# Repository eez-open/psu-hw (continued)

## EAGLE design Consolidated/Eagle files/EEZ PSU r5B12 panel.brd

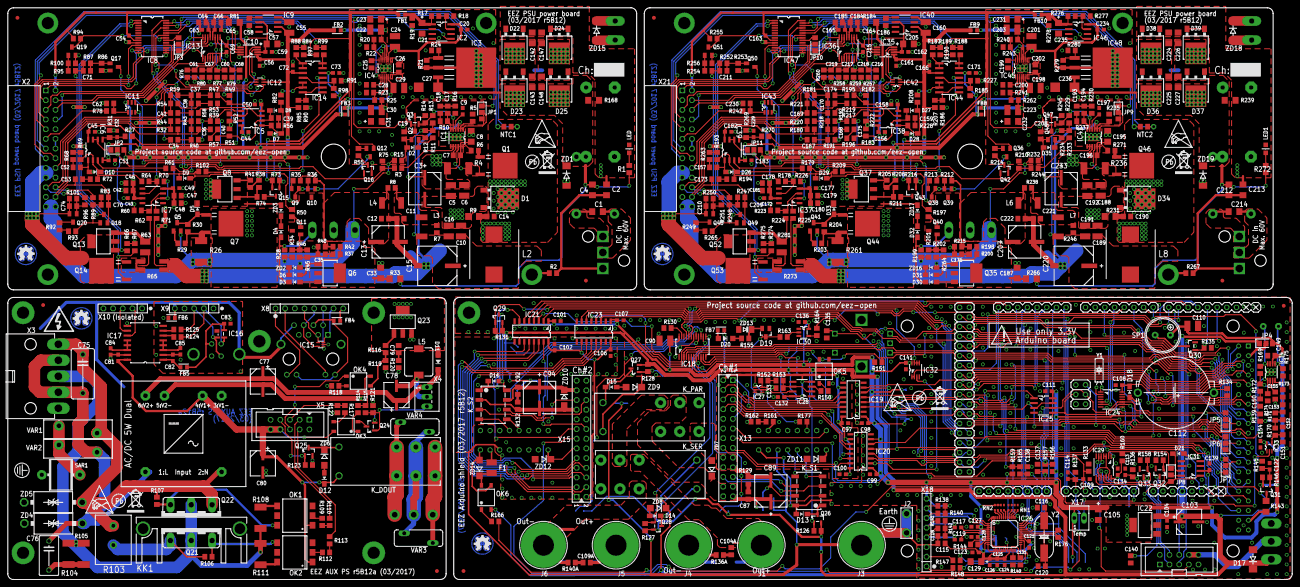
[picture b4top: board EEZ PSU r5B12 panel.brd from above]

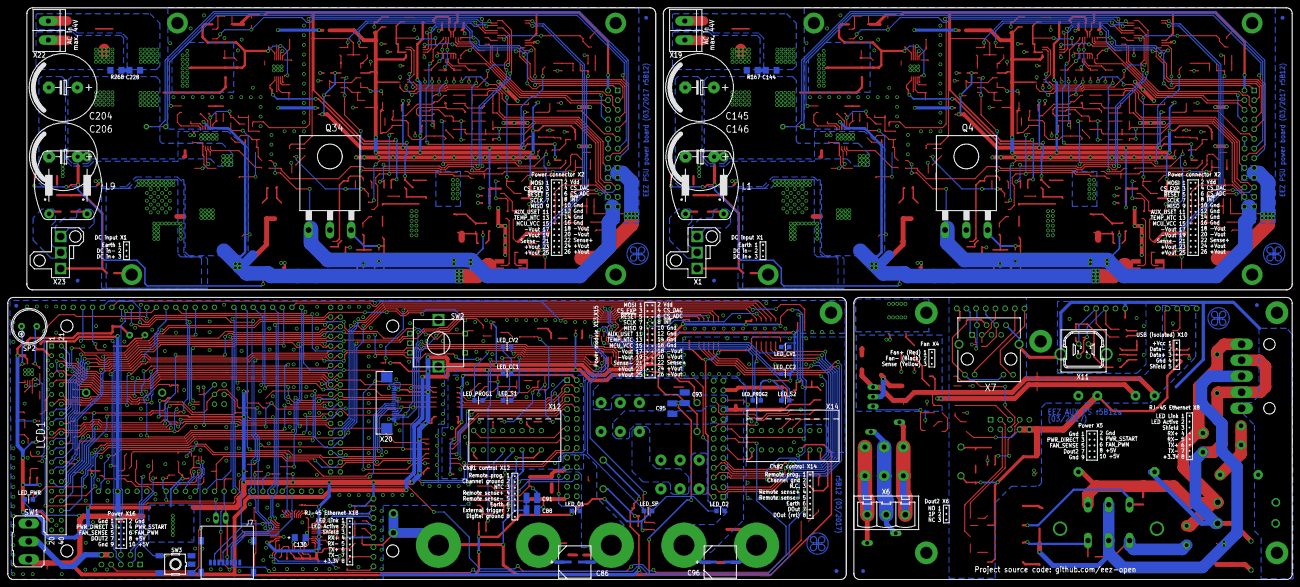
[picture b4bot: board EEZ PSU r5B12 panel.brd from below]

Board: 3 copper layers, 337.0 x 150.0 mm, 815 parts (42 on the bottom side), 579 nets.

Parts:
C1, C2, C4, C212, C213, C214: 4n7/100V; C1206
C3, C86, C96, C233: 50SVPF18M; CAPAE830X650N
C5, C6, C188, C192: 4u7/100V; C1210
C7, C87, C92, C150, C153, C196: 470n; C0805
C8, C33, C187, C195: 1u/100V; C1206
C9, C20, C32, C43, C44, C45, C49, C50, C51, C54, C56, C59, C63, C65, C69, C72, C73, C81, C82, C83, C84, C85, C97, C98, C99, C100, C101, C102, C104, C106, C107, C108, C109, C111, C113, C114, C121, C122, C123, C124, C125, C126, C127, C128, C132, C134, C136, C139, C141, C154, C156, C158, C161, C162, C163, C164, C165, C166, C171, C172, C177, C182, C183, C197, C215, C229, C234: 100n; C0603
C10, C16, C22, C24, C29, C30, C55, C90, C110, C160, C189, C191, C198, C201, C203, C223: 10u; C1210
C11, C26, C46, C48, C58, C64, C66, C104A, C109A, C149, C178, C180, C184, C185, C186, C202, C221: 1u; C0805
C12, C62, C222, C230: n.c.; C0805
C13, C207: EEEFK1H470P; CAPAE830X1050N
C14, C19, C190, C208: 470p; C0805
C15, C220: EEEFK1J101P; PANASONIC_F
C17, C39, C159, C194: 120p; C0805
C18, C151, C152, C193: 4n7; C0805
C21, C130, C235: 4u7; EC1206
C23, C31, C57, C105, C129, C205, C231, C232: 10u; EC1206
C25, C28, C35, C42, C47, C70, C74, C118, C131, C135, C137, C138, C176, C179, C181, C199, C200, C209, C210: 10n; C0805
C27, C236: 1uF/50V Tant.; C/6032-28R
C34, C41, C167, C169: 47p; C0805
C36, C37, C38, C40, C71, C168, C170, C174, C175, C211: 2n2; C0805
C52, C53, C157, C173: 1n; C0805
C60, C61, C67, C68, C216, C217, C218, C219: 3n3; C0805
C75: 6n8 (X1); C102-064X133
C76: 47n/400V; C075-052X106
C77, C80, C103: 47u; CAPAE660X610N
C78: 220u; CAPAE660X610N
C79, C133, C140: 47n; C0805
C88, C91, C93, C95: 4n7/100V; C1210
C89, C94: UWT1H220MCL; CAPAE830X650N
C112: EECS5R5H105; SG-R20MM
C115: 22n; C0805
C116, C120: 18p; C0805
C117, C119: 6n8; C0603
C142, C143, C147, C148, C224, C225, C226, C227: 1n; C1206
C144, C228: n.c; C1206
C145, C146, C204, C206: 2m2; ECAP7.5/18
C155: 220n; C0805
D1, D34: STPS15H100; TO252
D2, D3, D4, D5, D6, D7, D8, D9, D10, D12, D13, D14, D15, D16, D18, D21, D26, D27, D28, D29, D30, D31, D32, D33, D35: BAS316; SOD323-W
D11, D20: SKL16; SOD123
D17: SMBJ5.0A-TR; DO214AA
D19: BAT54S; SOT23
D22, D23, D24, D25, D36, D37, D38, D39: STPS15H100; TO252@1
EEZ_SIGNATURE, EEZ_SIGNATURE1, EEZ_SIGNATURE2, EEZ_SIGNATURE3: SIGNATURESMALL; SIGNATURE_5MM
F1: 50mA; F1210
FB1, FB2, FB3, FB4, FB5, FB6, FB7, FB8, FB9, FB10: 60R@100MHz; BEAD0603
FM1, FM2, FM3, FM4, FM5, FM6, FM7, FM8: FIDUCIAL_2; FIDUCIAL_DUAL
IC1, IC41: LTC3864EMSE#PBF; LTC_05-08-1666
IC2, IC46: LP2951SO8; SOIC127P600X175-8N
IC3, IC48: TL783CKTTR; TO254P1524X483-4N
IC4, IC45: LTC3260EMSE#PBF; SOP50P490X110-17N
IC5, IC6, IC38, IC39: TL072D; SOIC127P600X173-8N
IC7, IC37: LTC2050HVCS8#PBF; SOIC127P600X173-8N
IC8, IC47: MCP23S17-E/SS; SOP65P780X200-28N
IC9, IC40: REF5025AIDG4; SOIC127P600X175-8N
IC10, IC35: DAC8552IDGKTG4; DGK8-M
IC11, IC43: ADG465SOT-23; SOT95P280X145-6N
IC12, IC42: TS5A9411DCKT; SOT65P210X110-6N
IC13, IC36: ADS1120IPWR; PW(R-PDSO-G16)
IC14, IC44: LP339D; SOIC127P600X175-14N
IC15: TPD4E002DRL; DRL5
IC16: TPD2E001DZDR; SOP192P292X122-4N
IC17: ADUM3160BRWZ; SOIC-16W
IC18: TLC5925IDBQR; SOP63P600X175-24N
IC19, IC23: Si8641EC-B-IS1; SOIC-16
IC20, IC21: SI8651EC-B-IS1; SOIC-16
IC22: LD1117ADT33TR; SOT223
IC24: PCA21125T/Q900/1,1; SOP65P640X120-14N
IC25: AT25256B-SSHL-B; SOIC127P600X175-8N
IC26: W5500; TQFP48-7X7
IC27: BC857BS; SOT65P210X110-6N
IC28: TLC555; SOIC127P600X175-8N
IC29: SN74LVC08APWR; SOP65P640X120-14N
IC30: SN74LV1T34DBVR; SOT95P280X145-5N
IC31: TPS3705-33D; SOIC127P600X175-8N
IC32: SN74LVC2G02DCTR; SOP65P400X130-8N
IC33: 74LVC1G125GW.125; SOT65P210X110-5N
IC34: TPA6205A1DGN; SOP65P490X110-9N
J1, J5: BS-244DSM-R; BP_5_12
J2: 1-726388-2; PCB_TAB-4.8MM
J3: BS-244DSM-G; BP_5_12
J4, J6: BS-244DSM-B; BP_5_12
J7: 693072010801
JP1, JP2, JP3, JP4, JP5, JP6, JP7, JP8, JP9, JP10, JP11: 0R-JUMPA; A0R-JMP
KK1: SK 145/37,5; SK145
K_DOUT: RT424005; RT-C/016A5_ROUND
K_PAR: RT424005; RT-C/016A5_ROUND
K_S1, K_S2: G6K-2F-5DC; G6K-2F
K_SER: RT424005; RT-C/016A5_ROUND
L1, L9: RN112-4-02; RN112
L2, L8: 7443551331; WE-HCI_1350/1365
L3, L4, L6, L7: IHLP2020CZER3R3M11; IHLP-2020BZ-11
L5: 470u; DE0704
LCD1: TFT_320QVT; LCD_TFT_9341_MIRROR
LED, LED1: n.c.; LED_HSMH-C170
LED_CC1, LED_CC2: HSMH-C170; LED_HSMH-C170
LED_CV1, LED_CV2: HSMY-C170; LED_0805
LED_O1, LED_O2: HSMG-C170; LED_0805
LED_PROG1, LED_PROG2: HSMH-C170; LED_HSMH-C170
LED_PWR: HSMD-C170; LED_0805
LED_S1, LED_S2: HSMY-C170; LED_0805
LED_SP: HSMH-C170; LED_HSMH-C170
MCU: Arduino Due; ARDUINO+ICSP_MIRROR
NTC1, NTC2: 10K/Beta:3570K; R_0204/5+0805
OK1: MOC3052; DIL6-SMD
OK2: MOC3062; DIL6-SMD
OK3, OK4, OK5, OK6: HCPL-181
Q1, Q7, Q44, Q46: IRFR5305; TO229P990X239-3N
Q2, Q9, Q10, Q18, Q38, Q39, Q45, Q49: MMBT5401; SOT23-BEC
Q3, Q16, Q24, Q25, Q30, Q32, Q33, Q42, Q47: 2N7002; SOT103P240X110-3N
Q4, Q34: IRFP250N; TO247BH-CLR
Q5, Q41: BC857C; SOT23-BEC
Q6, Q8, Q35, Q37: BCP56-16.115; SOT230P700X180-4N
Q11, Q12, Q17, Q19, Q20, Q36, Q40, Q48, Q50, Q51: MMBT5551; SOT23-BEC
Q13, Q23, Q52: IRLL2705PBF; SOT223
Q14, Q53: IRFR48ZPBF; TO229P990X239-3N
Q15, Q26, Q27, Q28, Q29, Q31, Q43: IRLML2246TRPBF; SOT95P237X112-3N
Q21, Q22: BTA26-600; TOP3S-1
R1, R2, R14, R160, R245, R267, R272: n.c.; R0805
R3, R10, R11, R19, R27, R40, R49, R51, R58, R64, R69, R72, R74, R82, R91, R94, R95, R98, R102, R121, R122, R139, R145, R149, R157, R165, R172, R173, R178, R182, R183, R185, R191, R192, R193, R194, R208, R209, R211, R227, R233, R237, R244, R254, R255, R270, R278: 10K; R0805
R4, R236: R010/2W; R2512
R5, R66, R67, R85, R86, R87, R100, R154, R158, R174, R207, R235, R252, R253, R256, R274, R275: 47K; R0805
R6, R129, R132, R136A, R140A, R271: 1R; R0805
R7, R8, R42, R116, R155, R198, R238, R246: 100R; R0805
R9, R33, R81, R143, R184, R231, R266: 10R; R1206
R12, R15, R22, R23, R73, R75, R123, R135, R146, R210, R216, R232, R234, R241, R243: 100K; R0805
R13, R20, R25, R229, R240, R262: 330K; R0805
R16, R126, R127, R128, R131, R133, R136, R137, R156, R159, R161, R162, R230: 4K7; R0805
R17, R34, R201, R276: 16K; R0805
R18, R84, R97, R189, R190, R277: 5K1; R0805
R21, R31, R35, R36, R41, R47, R57, R76, R77, R79, R80, R110, R113, R118, R166, R177, R195, R196, R205, R212, R213, R257, R258, R259, R260, R269, R279: 220R; R0805
R24, R55, R130, R151, R214, R280: 1K8; R0805
R26, R261: 2R2/2W; R2512
R28, R38, R68, R78, R92, R114, R120, R163, R164, R170, R171, R199, R206, R242, R249, R263: 1K; R0805
R29, R30, R32, R45, R59, R61, R90, R93, R106, R107, R119, R179, R180, R181, R186, R203, R204, R264, R265: 2K2; R0805
R37, R50, R197, R200: 470R; R0805
R39, R52, R217, R222: 7K5 0.1%; R0805
R43, R53, R218, R219: 100K 0.1%; R0805
R44, R54, R220, R221: 24K 0.1%; R0805
R46, R89, R96, R152, R153, R202, R248, R251: 750R; R0805
R48, R215: 51K; R0805
R56, R228: 0R; R0805
R60, R70, R223, R226: 2K 0.1%; R0805
R62, R71, R224, R225: 82R 0.1%; R0805
R63, R281: 0R16; R1210
R65, R273: 0R020 (1-3W); R_2512-4WIRE
R83, R101, R247, R250: 330R; R0805
R88, R99, R115, R117, R187, R188: 5K6; R0805
R103: 18-22R/7W; R_0913
R104, R105, R108, R111: 330R/2W; R2512
R109, R112, R138, R140, R141, R142: 49R9; R0805
R124, R125: 22R; R0805
R134, R147, R148, R150: 180R; R0805
R144: 12K4; R0805
R167, R268: n.c.; R1206
R168, R239: 12K; R1206
R169, R175: 20K; R0805
R176: 1M; R0805
RN1, RN2: 4x10K; CAY16
SAR1: CG2-470L; SAR
SH1, SH4: Pgnd to Pout- short; SHORT_NOHOLE
SH2, SH5: Sgnd to Pgnd short; SHORT_NOHOLE
SH3: SHORT_NOHOLE
SP1, SP2: LD-BZEN-0903
SW1: A101SYCQ04; M9040P
SW2: PEC12R-4225F-S0024; EC12E_SW
SW3: 1301.9316; TACTM-6XN
TR1: VTX-214-005-0512; PCB_ACDC_VTX_5W_DUAL
U$1, U$2, U$8, U$11: RECYCLE_BIN1/8
U$3, U$5, U$9, U$12: PB_SMALL
U$4, U$6, U$7, U$10: ESD_SYMBOL
VAR1, VAR2: ERZE14A431; VARISTOR
VAR3, VAR4: ERZE11A431; VARISTOR_13MM
X1, X23: 39-30-1039; MINIFIT_39301039
X2, X21: SSW-113-02-T-D-RA
X3: 39303055; MINIFIT_6659-5
X4: 22-23-2031
X5, X16: 09185067324; IDC-10PIN
X6: CTB9300/3A + CTB92VG/3S; WR-TBL_3-PIN
X7: Amphenol: LMJ2138812S0LOT6C or WE: 74990101210; RJ45-VERT
X8: 826629-8; HEADER_8-PIN
X9, X10: 826629-5; SSW-105-02-S-S
X11: 2411-01; KUSBVX-BS1N
X12, X14: MC000006; MC000006_MIRROR
X13, X15: TSW-113-07-F-D
X17: 22-23-2021
X18: MC34753; HEADER_8-PIN
X19, X22: 282836-2; TBLOCK5.0_2
X20: PCA-6B-20-HL-3 or 52746-2071; FPC-20_ROTATED
Y1: 32.768kHz; R26_XTAL
Y2: 25MHz; HC-49/4H
ZD1, ZD19: SMAJ51A; DO214AA
ZD2, ZD16: BZX384-C15; SOD323-W
ZD3, ZD17: PDZ6.2B; SOD323-W
ZD4, ZD5: 1.5KE400CA; DO201-BIDIR
ZD6, ZD8, ZD9, ZD11, ZD12, ZD14: SMAJ18A; DO214AC
ZD7, ZD10: P4SMAJ48A; DO214AC
ZD13: 4V3; MINIMELF
ZD15, ZD18: n.c.; DO214AA

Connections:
0V: C77.2, Q23.3, Q24.2, R119.1, R120.1, R121.2, TR1.5
1V2O: C131.2, IC26.22
!ADC1_SELECT: IC20.4, MCU.15
!ADC2_SELECT: IC23.4, MCU.48
!BP_OE: IC18.21, MCU.10
!BP_OUT0: IC18.5, LED_CV1.C
!BP_OUT1: IC18.6, Q26.1, R126.1
!BP_OUT2: IC18.7, LED_O1.C
!BP_OUT3: IC18.8, LED_SP.C
!BP_OUT4: IC18.9, LED_PROG1.C
!BP_OUT5: IC18.10, LED_S1.C
!BP_OUT6: IC18.11, LED_CC1.C
!BP_OUT7: IC18.12, LED_CV2.C
!BP_OUT8: IC18.13, Q28.1, R127.1
!BP_OUT9: IC18.14, Q27.1, R128.1
!BP_OUT10: IC18.15, LED_CC2.C
!BP_OUT12: IC18.17, LED_S2.C
!BP_OUT13: IC18.18, LED_O2.C
!BP_OUT14: IC18.19, Q29.1, R131.1
!BP_OUT15: IC18.20, LED_PWR.C
!CH1_ADC: IC20.13, X13.6
!CH1_DAC: IC19.12, X13.4
!CH1_EXPANDER: IC19.13, X13.3
!CH1_INT: IC20.11, X13.8
!CH1_RESET: IC20.14, X13.5
!CH2_ADC: IC23.13, X15.6
!CH2_DAC: IC21.12, X15.4
!CH2_EXPANDER: IC21.13, X15.3
!CH2_INT: IC21.11, X15.8
!CH2_RESET: IC23.14, X15.5
!CONVEND1: IC20.6, MCU.21
!CONVEND2: IC21.6, MCU.20
!DAC1_SELECT: IC19.5, MCU.16
!DAC2_SELECT: IC21.5, MCU.47
!DP_DRIVE: Q8.1, R38.1, R74.1
!DP_DRIVE1: Q37.1, R206.1, R211.1
!EEPROM_SELECT: IC25.1, MCU.49
!ETH_IRQ: IC26.36, MCU.18
!ETH_SELECT: IC26.32, MCU.11
!INT: JP3.2, X2.8
!INT1: JP10.2, X21.8
!IO_EXPANDER1: IC19.4, MCU.17
!IO_EXPANDER2: IC21.4, MCU.46
!LCD_INT: MCU.50, X20.7
!LCD_PD: MCU.51, X20.8
!MR: C140.2, IC31.1, JP8.1, SW3.3, SW3.4
!PS_DRDY: IC13.14, JP3.3
!PS_DRDY1: IC36.14, JP10.3
!PS_RESET: IC8.18, X2.5
!PS_RESET1: IC47.18, X21.5
!RESET: D21.A, IC20.3, IC23.3, IC26.37, IC29.1, MCU.RESET
!RST_OUT: IC29.3, IC29.4, IC29.9, IC29.13
!RTC_IRQ: IC24.5, MCU.19
!SET_100%: IC8.24, Q3.1
!SET_100%1: IC47.24, Q47.1
!SET_DP: IC8.22, Q15.1, R73.2
!SET_DP1: IC47.22, Q43.1, R216.2
+3V3: C90.1, C98.1, C99.1, C101.1, C105.+, C107.1, C110.2, C111.1, C115.1, C121.2, C123.1, C124.1, C125.1, C126.1, C127.1, C128.1, C129.+, C134.2, C136.1, C139.2, C141.1, C149.2, C154.2, D18.A, IC18.24, IC19.1, IC20.1, IC20.7, IC21.1, IC21.7, IC22.4, IC23.1, IC25.3, IC25.7, IC25.8, IC26.4, IC26.8, IC26.11, IC26.15, IC26.17, IC26.21, IC26.28, IC29.14, IC30.5, IC31.2, IC32.8, IC33.5, IC34.6, J7.4, JP4.3, Q31.2, R138.1, R139.2, R140.2, R146.2, R151.1, R156.1, R159.1, R160.2, RN2.6, RN2.7, RN2.8, SP1.+B, X13.15, X15.15, X17.1, X18.8, X20.1, X20.17, X20.18
+5V: C54.1, C63.2, C64.2, C80.1, C81.1, C103.1, C104.1, D12.C, D17.C, FB1.P$2, FB7.P$1, IC8.9, IC13.13, IC17.16, IC22.3, JP4.1, K_DOUT.A1, LED_CC1.A, LED_CC2.A, LED_CV1.A, LED_CV2.A, LED_O1.A, LED_O2.A, LED_PROG1.A, LED_PROG2.A, LED_PWR.A, LED_S1.A, LED_S2.A, LED_SP.A, MCU.5V, OK1.1, OK2.1, OK3.4, Q12.B, Q15.2, Q26.2, Q27.2, Q28.2, Q29.2, R73.1, R84.2, R94.2, R97.2, R126.2, R127.2, R128.2, R131.2, SW1.3, TR1.4, X2.2, X5.8, X5.10
+5V1: C163.1, C165.2, C185.2, FB10.P$2, IC36.13, IC47.9, Q36.B, Q43.2, R189.2, R190.2, R216.1, R255.2, X21.2
+12VDC: C77.1, C78.1, D11.C, OK4.4, R114.1, R115.1, TR1.6, X4.1
+VNR: C20.1, C24.1, IC2.8, IC3.2, IC3.4, IC4.1, IC4.11, IC4.13, R21.1
+VNR1: C201.1, C234.1, IC45.1, IC45.11, IC45.13, IC46.8, IC48.2, IC48.4, R279.1
+VREF: C57.+, C59.2, C69.2, IC9.6, IC10.2, IC13.9, R27.1
+VREF1: C162.2, C205.+, C215.2, IC35.2, IC36.9, IC40.6, R270.1
-5VOUT: C30.2, C31.-, FB3.P$1, IC4.5, R25.2
-5VOUT1: C223.2, C232.-, FB8.P$1, IC45.5, R262.2
-12V: C29.1, IC4.6, R38.2, R41.2
-12V1: C198.1, IC45.6, R205.2, R206.2
AC_EARTH: FB6.P$1, SAR1.P$2, X3.1, X7.8, X7.SH1, X7.SH2, X9.5, X11.M1, X11.M2, ZD4.C, ZD5.C
AC_IN1: C147.1, C148.2, D24.3, D25.1, D25.2, R167.2, X19.1, ZD15.A
AC_IN2: C142.1, C143.2, C144.1, D22.3, D23.1, D23.2, X19.2, ZD15.C
AC_IN3: C224.1, C225.2, C228.1, D36.1, D36.2, D38.3, X22.2, ZD18.C
AC_IN4: C226.1, C227.2, D37.1, D37.2, D39.3, R268.2, X22.1, ZD18.A
AC_IN_L: C75.1, Q22.A1, R103.1, R107.2, TR1.2, VAR1.P$2, X3.5, ZD5.A
AC_NEUTRAL: C75.2, C76.1, TR1.1, VAR2.P$1, X3.2, X3.4, ZD4.A
AC_OUT_L: Q21.A2, Q22.A2, R104.1, R105.1, R108.2, R111.2, X3.3
AUDIO_OUT: IC33.2, X20.10
AUX1_USET_IN: X12.8, X12.8.1, X13.11, ZD11.C
AUX2_USET_IN: X14.8, X14.8.1, X15.11, ZD12.C
AUX_+3V3: FB4.P$2, X8.8
AUX_ETH_ACTLED: X7.10, X8.2
AUX_ETH_IN+: IC15.4, X7.3, X8.4
AUX_ETH_IN-: IC15.5, X7.6, X8.5
AUX_ETH_LINKLED: X7.12, X8.1
AUX_ETH_OUT+: IC15.1, X7.2, X8.6
AUX_ETH_OUT-: IC15.3, X7.1, X8.7
AUX_FAN_CTRL: OK4.1, X5.6
AUX_FAN_SENSE: R117.2, R122.1, X5.5
AUX_PWR_DIRECT: R110.2, X5.3
AUX_PWR_SSTART: R113.2, X5.4
AUX_USET_IN: R78.2, X2.11
AUX_USET_IN1: R242.2, X21.11
AUX_USET_SW: IC8.25, IC12.1
AUX_USET_SW1: IC42.1, IC47.25
BATT_NTC: MCU.A4, OK5.4, R151.2
BP_SELECT: IC18.4, MCU.9
BUZZER: MCU.12, Q30.1, R135.2
CC_ACTIVE: IC8.23, R97.1, R99.2
CC_ACTIVE1: IC47.23, R188.2, R190.1
CH1_GND: C97.2, C100.2, C132.2, C133.1, IC19.9, IC19.15, IC20.9, IC28.1, OK5.2, X12.7, X12.7.1, X13.10, X13.12, X13.14, ZD11.A
CH1_MISO: IC19.11, X13.9
CH1_MOSI: IC19.14, X13.1
CH1_SCLK: IC20.12, X13.7
CH1_SYNC: IC20.15, X13.16
CH1_VDD: C97.1, C100.1, C132.1, IC19.10, IC19.16, IC20.10, IC20.16, IC27.1, IC27.4, IC28.4, IC28.8, X13.2
CH2_GND: C102.2, C106.2, IC21.9, IC23.9, IC23.15, X14.7, X14.7.1, X15.10, X15.12, X15.14, ZD12.A
CH2_MISO: IC23.11, X15.9
CH2_MOSI: IC21.14, X15.1
CH2_SCLK: IC23.12, X15.7
CH2_SYNC: IC21.15, X15.16
CH2_VDD: C102.1, C106.1, IC21.10, IC21.16, IC23.10, IC23.16, X15.2
CS_ADC: IC13.2, X2.6
CS_ADC1: IC36.2, X21.6
CS_DAC: IC10.5, X2.4
CS_DAC1: IC35.5, X21.4
CS_EXPANDER: IC8.11, X2.3
CS_EXPANDER1: IC47.11, X21.3
CURR_5A: IC8.1, Q14.1, R67.2
CURR_5A1: IC47.1, Q53.1, R274.2
CURR_500MA: IC8.2, Q13.1, R66.2
CURR_500MA1: IC47.2, Q52.1, R275.2
CV_ACTIVE: IC8.26, R84.1, R88.2
CV_ACTIVE1: IC47.26, R187.2, R189.1
D+: IC16.2, R125.1, X9.3, X11.3
D-: IC16.3, R124.1, X9.2, X11.2
DC+: C1.2, L1.2, X1.3
DC+1: C214.2, L9.2, X23.3
DC-: C1.1, L1.1, X1.2
DC-1: C214.1, L9.1, X23.2
DC_BIAS: C33.1, Q6.2, Q6.4, R33.2, R35.2, R36.2
DC_BIAS1: C187.1, Q35.2, Q35.4, R212.2, R213.2, R266.2
DC_OUT: C3.1, C4.2, C5.1, C6.1, C7.2, C8.1, C27.+, C143.1, C145.+, C146.+, C148.1, D23.3, D25.3, IC1.11, IC3.3, L1.3, R1.2, R4.1, R33.1, R168.1, ZD1.C
DC_OUT1: C188.1, C192.1, C195.1, C196.2, C204.+, C206.+, C212.2, C225.1, C227.1, C233.1, C236.+, D36.3, D37.3, IC41.11, IC48.3, L9.3, R236.1, R239.1, R266.1, R272.2, ZD19.C
DOUT1: MCU.A11, R166.1
DOUT2: IC29.5, MCU.A3
DP_LED: Q15.3, R74.2
DP_LED1: Q43.3, R211.2
EARTH: C2.2, C4.1, C88.2, C91.1, C93.2, C95.1, C115.2, C118.2, J2.P$1, J2.P$2, J3.P$1, R2.2, X1.1, X12.3, X12.3.1, X14.3, X14.3.1, X18.3
EARTH1: C212.1, C213.2, R267.2, X23.1
ENC_A: C137.2, MCU.A8, R157.1
ENC_B: C138.1, MCU.A9, R165.1
ENC_SW: C135.2, MCU.A10, SW2.D
ETH_ACTLED: IC26.27, R147.1
ETH_IN+: C119.1, R142.1, X18.4
ETH_IN-: C117.1, R141.2, X18.5
ETH_LINKLED: IC26.25, R148.1
ETH_OUT+: IC26.2, R140.1, X18.6
ETH_OUT-: IC26.1, R138.2, X18.7
EXTSD_CS: J7.2, MCU.A12
EXT_TRIG: MCU.A7, R164.1
FAN_OUT: C79.2, D11.A, L5.2, Q23.2, Q23.4
FAN_PWM: MCU.6, X16.6
FAN_SENSE: MCU.13, X16.5
FB: IC1.5, Q3.2, R13.2, R14.2, R16.1
FB1: IC41.5, Q47.2, R229.2, R230.1, R245.2
GCOM: JP2.2, R39.1, R60.1
GCOM1: JP11.2, R217.1, R223.1
GND: C2.1, C3.2, C5.2, C6.2, C8.2, C10.2, C15.2, C16.2, C20.2, C21.-, C22.2, C23.-, C24.2, C25.1, C27.-, C28.1, C29.2, C30.1, C31.+, C32.2, C33.2, C35.2, C42.1, C43.2, C44.1, C45.1, C46.1, C47.1, C48.1, C49.2, C50.1, C51.1, C54.2, C55.2, C56.1, C57.-, C58.2, C59.1, C60.1, C61.2, C62.1, C63.1, C64.1, C65.1, C66.1, C67.1, C68.1, C69.1, C72.1, C73.1, C80.2, C81.2, C84.2, C90.2, C98.2, C99.2, C101.2, C103.2, C104.2, C105.-, C107.2, C108.1, C109.1, C110.1, C111.2, C112.2, C113.1, C114.1, C116.2, C120.2, C121.1, C122.1, C123.2, C124.2, C125.2, C126.2, C127.2, C128.2, C129.-, C131.1, C134.1, C135.1, C136.2, C137.1, C138.2, C139.1, C140.1, C141.2, C142.2, C145.-, C146.-, C147.2, C149.1, C150.2, C151.2, C152.2, C154.1, C155.1, D1.1, D1.2, D13.A, D16.A, D17.A, D19.1, D22.1, D22.2, D24.1, D24.2, IC1.TP, IC2.4, IC4.2, IC4.14, IC4.17, IC8.10, IC8.15, IC8.16, IC8.17, IC9.4, IC10.8, IC12.3, IC13.3, IC13.4, IC13.5, IC13.8, IC15.2, IC17.9, IC17.15, IC18.1, IC19.2, IC19.8, IC20.8, IC21.8, IC22.1, IC23.2, IC23.8, IC24.7, IC25.4, IC26.29, IC29.7, IC30.3, IC31.3, IC31.4, IC32.4, IC33.1, IC33.3, IC34.7, IC34.TP, J7.6, J7.Z1, J7.Z2, JP2.3, K_PAR.A1, K_S1.8, K_S2.8, K_SER.A1, L1.4, LCD1.1, LED.C, MCU.GND, MCU.GND1, MCU.GND2, MCU.GND3, MCU.GND4, MCU.ICSP_GND, OK5.3, OK6.2, Q7.2, Q16.2, Q17.E, Q19.E, Q25.2, Q30.2, Q32.2, Q33.2, R9.1, R18.2, R22.2, R23.1, R24.2, R31.2, R45.1, R46.1, R48.1, R66.1, R67.1, R75.1, R86.1, R90.1, R91.2, R100.1, R118.2, R122.2, R123.1, R130.1, R133.2, R135.1, R136.2, R137.2, R149.1, R154.2, R158.2, R168.2, R174.2, RN1.5, RN1.6, RN1.7, RN1.8, RN2.5, SH1.P$2, SH2.P$2, SH3.P$1, SW2.C, SW2.E, SW2.GND1, SW2.GND2, SW3.1, SW3.2, SW3.5, TR1.3, X2.10, X2.12, X2.14, X5.1, X5.2, X5.9, X10.4, X12.1, X12.1.1, X16.1, X16.2, X16.9, X20.2, X20.19, X20.20, ZD1.A, ZD8.C, ZD9.C, ZD13.A
GND1: C156.1, C158.1, C160.2, C161.1, C162.1, C163.2, C164.1, C165.1, C166.1, C171.1, C172.2, C176.2, C177.2, C178.1, C179.1, C180.1, C181.1, C182.1, C183.1, C184.1, C185.1, C186.2, C187.2, C188.2, C189.2, C191.2, C192.2, C195.2, C198.2, C199.1, C200.1, C201.2, C203.2, C204.-, C205.-, C206.-, C213.1, C215.1, C216.1, C217.1, C218.1, C219.2, C220.2, C223.1, C224.2, C226.2, C229.2, C230.1, C231.-, C232.+, C233.2, C234.2, C235.-, C236.-, D34.1, D34.2, D38.1, D38.2, D39.1, D39.2, IC35.8, IC36.3, IC36.4, IC36.5, IC36.8, IC40.4, IC41.TP, IC42.3, IC45.2, IC45.14, IC45.17, IC46.4, IC47.10, IC47.15, IC47.16, IC47.17, JP11.3, L9.4, LED1.C, Q42.2, Q44.2, Q50.E, Q51.E, R186.1, R202.1, R210.1, R215.1, R227.2, R231.1, R239.2, R241.1, R243.2, R253.1, R256.1, R264.1, R269.2, R274.1, R275.1, R277.2, R280.2, SH4.P$2, SH5.P$2, X21.10, X21.12, X21.14, ZD19.A
GNDA: C130.-, IC26.3, IC26.9, IC26.14, IC26.16, IC26.19, IC26.48, R144.1, SH3.P$2
INT_EXP: IC8.20, JP3.1
INT_EXP1: IC47.20, JP10.1
ISENSE+: IC7.3, R60.2, R62.2
ISENSE+1: IC37.3, R223.2, R224.2
ISENSE-: IC7.2, R70.1, R71.2
ISENSE-1: IC37.2, R225.2, R226.1
ISOLATOR1_EN: IC19.7, MCU.14
ISOLATOR2_EN: IC23.7, MCU.45
I_MON: IC7.6, R64.1, R70.2, R80.1
I_MON1: IC37.6, R178.1, R226.2, R258.1
I_SERVO: C52.2, D9.C, D10.A, IC6.1, R102.1
I_SERVO1: C157.2, D26.A, D29.C, IC39.1, R209.1
I_SET: IC10.3, R61.1, R76.1
I_SET1: IC35.3, R179.1, R260.1
LCDSD_CS: LCD1.38, MCU.53, X20.9
LCD_BRIGHTNESS: MCU.7, R145.1
LCD_CS: LCD1.15, MCU.39, X20.6
LCD_DB0: LCD1.21, MCU.37
LCD_DB1: LCD1.22, MCU.36
LCD_DB2: LCD1.23, MCU.35
LCD_DB3: LCD1.24, MCU.34
LCD_DB4: LCD1.25, MCU.33
LCD_DB5: LCD1.26, MCU.32
LCD_DB6: LCD1.27, MCU.31
LCD_DB7: LCD1.28, MCU.30
LCD_DB8: LCD1.7, MCU.22
LCD_DB9: LCD1.8, MCU.23
LCD_DB10: LCD1.9, MCU.24
LCD_DB11: LCD1.10, MCU.25
LCD_DB12: LCD1.11, MCU.26
LCD_DB13: LCD1.12, MCU.27
LCD_DB14: LCD1.13, MCU.28
LCD_DB15: LCD1.14, MCU.29
LCD_RD: LCD1.6, R139.1
LCD_RESET: LCD1.17, MCU.38
LCD_RS: LCD1.4, MCU.41
LCD_WR: LCD1.5, MCU.40
LED_A: LCD1.19, R143.2
LOOP_CTRL: D7.A, D9.A, R50.1
LOOP_CTRL1: D28.A, D29.A, R197.1
L_OUT: C10.1, C15.1, C16.1, L2.2, L3.1, R7.1, R11.1, R12.1, R13.1
L_OUT12: C189.1, C191.1, C220.1, L7.1, L8.2, R229.1, R233.1, R234.1, R246.1
MCU_D+: IC17.10, X10.3
MCU_D-: IC17.11, X10.2
MCU_VCC: NTC1.2, NTC1.2.1, X2.15
MCU_VCC1: NTC2.2, NTC2.2.1, X21.15
MISO: IC19.6, IC23.6, IC24.8, IC25.2, IC26.34, J7.7, JP7.1, LCD1.35, MCU.ICSP_MISO, X20.4
MODE: IC1.1, JP1.2
MODE1: IC41.1, JP9.2
MOSI: IC18.2, IC19.3, IC21.3, IC24.9, IC25.5, IC26.35, J7.3, JP6.1, LCD1.37, MCU.ICSP_MOSI, X20.5
unnamed: Q8.3, R41.1
unnamed: Q5.B, R29.2
unnamed: C34.2, R40.1
unnamed: R68.2, R69.1
unnamed: C22.1, C23.+, FB2.P$1, IC4.12, R20.1
unnamed: C52.1, R68.1
unnamed: C26.1, IC4.9, IC4.10
unnamed: C144.2, R167.1
unnamed: IC11.4, IC12.6
unnamed: C41.2, R58.1
unnamed: C58.1, IC9.5
unnamed: C62.2, IC11.1, R78.1
unnamed: C32.1, IC6.5, R27.2, R31.1
unnamed: IC4.15, R20.2, R22.1
unnamed: Q1.1, R6.2
unnamed: IC6.6, IC6.7, JP2.1
unnamed: C38.1, R53.2, R54.1
unnamed: C39.2, R56.1
unnamed: D2.C, Q2.E, R11.2
unnamed: C17.1, IC1.6, R10.2
unnamed: C18.1, R10.1
unnamed: C53.2, R72.1
unnamed: C7.1, IC1.9
unnamed: IC34.5, R175.1, SP2.+B
unnamed: C70.2, Q18.B, R83.1, R89.2, R93.2
unnamed: C37.2, R47.1
unnamed: C40.2, R57.1
unnamed: C68.2, IC13.10, R79.2
unnamed: IC5.3, R47.2, R49.2
unnamed: IC1.12, R6.1
unnamed: IC1.2, R5.1
unnamed: C39.1, D8.C, IC5.2, R51.2, R57.2
unnamed: C9.2, IC1.4
unnamed: C19.1, Q2.C, Q3.3, R14.1
unnamed: C11.1, L3.2, L4.1, R7.2, R8.1
unnamed: IC1.8, R3.1
unnamed: D10.C, IC6.2, R64.2, R69.2, R72.2
unnamed: C14.2, R9.2
unnamed: Q19.B, R95.1, R100.2
unnamed: C71.2, Q18.C, R87.1, R95.2
unnamed: C60.2, IC13.11, R77.2
unnamed: C65.2, C66.2, IC13.12, R81.2
unnamed: C26.2, IC4.7, IC4.8
unnamed: Q11.B, R34.1, R45.2, R46.2
unnamed: IC14.1, IC14.2, R88.1
unnamed: IC3.1, R21.2, R24.1
unnamed: Q20.C, R92.1
unnamed: IC14.13, IC14.14, R99.1
unnamed: C74.1, Q20.B, R96.1, R101.2
unnamed: IC6.3, R61.2
unnamed: C61.1, IC13.6, R76.2
unnamed: C25.2, IC4.16
unnamed: C71.1, Q17.B, R86.2, R87.2
unnamed: FB4.P$1, X7.4, X7.9, X7.11
unnamed: C67.2, IC13.7, R80.2
unnamed: D3.C, D4.A, Q4.G, R28.1
unnamed: IC4.4, R23.2, R25.1
unnamed: C28.2, IC4.3
unnamed: F1.2, X14.2, X14.2.1
unnamed: IC27.2, IC27.3, IC27.5, R177.2
unnamed: OK3.3, R117.1
unnamed: D3.A, Q6.3
unnamed: IC2.7, R17.2, R18.1
unnamed: K_DOUT.14A, K_DOUT.14B, VAR3.2, X6.1
unnamed: D6.A, Q6.1, R37.2, R42.1
unnamed: Q24.1, R115.2, R121.1, X4.3
unnamed: C35.1, R37.1
unnamed: K_DOUT.11A, K_DOUT.11B, VAR3.1, VAR4.1, X6.2
unnamed: Q25.1, R123.2, X5.7
unnamed: R63.1, R65.2S
unnamed: OK1.6, Q22.G, R107.1
unnamed: OK2.4, Q21.G, R106.2
unnamed: OK2.6, R111.1
unnamed: R109.2, R110.1
unnamed: R112.2, R113.1
unnamed: OK1.4, R108.1
unnamed: D12.A, ZD6.A
unnamed: LED.A, R1.1
unnamed: C19.2, D2.A, Q2.B, R12.2, R15.1
unnamed: K_DOUT.A2, Q25.3, ZD6.C
unnamed: OK4.2, R118.1
unnamed: IC29.8, Q32.1, R154.1
unnamed: C76.2, R104.2, R105.2
unnamed: C79.1, R120.2
unnamed: Q23.1, R116.1
unnamed: C78.2, L5.1, X4.2
unnamed: C85.1, IC17.3, IC17.4, IC17.5
unnamed: IC17.6, R124.2
unnamed: IC17.7, R125.2
unnamed: C82.1, FB5.P$2, IC17.1
unnamed: C84.1, IC17.12, IC17.13, IC17.14
unnamed: D13.C, K_S1.1, Q26.3
unnamed: D16.C, K_S2.1, Q29.3
unnamed: C87.2, R129.2
unnamed: C92.2, R132.2
unnamed: IC18.16, LED_PROG2.C
unnamed: K_SER.14A, K_SER.14B
unnamed: K_PAR.12A, K_SER.11B
unnamed: K_PAR.12B, K_SER.11A
unnamed: SW1.2, X16.8, X16.10
unnamed: Q30.3, SP1.-B
unnamed: JP4.2, LCD1.2
unnamed: Q31.3, R143.1
unnamed: JP7.2, LCD1.33
unnamed: JP5.2, LCD1.29
unnamed: JP6.2, LCD1.31
unnamed: C112.1, R134.1
unnamed: IC26.23, R149.2
unnamed: C108.2, D18.C, IC24.14, R134.2
unnamed: IC26.10, R144.2
unnamed: C116.1, IC26.31, R176.2, Y2.1
unnamed: C120.1, IC26.30, R176.1, Y2.2
unnamed: C117.2, IC26.5
unnamed: SAR1.P$1, VAR1.P$1, VAR2.P$2
unnamed: C119.2, IC26.6
unnamed: R148.2, X18.1
unnamed: C36.1, R43.2, R44.1
unnamed: R147.2, X18.2
unnamed: IC26.43, RN2.3
unnamed: IC26.44, RN2.2
unnamed: IC26.45, RN2.1
unnamed: IC26.42, RN2.4
unnamed: IC26.38, RN1.4
unnamed: C118.1, R141.1, R142.2
unnamed: IC39.3, R179.2
unnamed: IC26.39, RN1.3
unnamed: IC26.41, RN1.1
unnamed: D14.A, ZD8.A
unnamed: D6.C, ZD2.C
unnamed: IC26.40, RN1.2
unnamed: D15.A, ZD9.A
unnamed: C122.2, Q31.1, R145.2, R146.1
unnamed: IC24.1, Y1.2
unnamed: IC24.2, Y1.1
unnamed: IC29.6, X16.7
unnamed: C133.2, IC28.2, IC28.6, R153.2
unnamed: IC27.6, IC28.7, R152.1
unnamed: OK5.1, R150.2
unnamed: D19.3, R162.1, R163.2
unnamed: IC30.2, R163.1
unnamed: IC30.4, R164.2
unnamed: R161.2, X12.2, X12.2.1
unnamed: D4.C, ZD3.C
unnamed: D19.2, R155.1, ZD13.C
unnamed: Q11.E, R50.2
unnamed: Q7.3, R26.1, R29.1, R30.1
unnamed: D5.A, Q5.C, Q7.1, R30.2
unnamed: D20.C, R155.2
unnamed: D20.A, FB7.P$2
unnamed: IC5.5, R39.2, R40.2, R43.1
unnamed: IC31.8, JP8.2
unnamed: Q21.A1, R103.2, R106.1
unnamed: IC14.5, IC14.6, R82.2
unnamed: IC38.3, R182.2, R195.2
unnamed: D14.C, K_SER.A2, Q28.3
unnamed: D15.C, K_PAR.A2, Q27.3
unnamed: R156.2, R157.2, SW2.B
unnamed: IC5.6, R52.2, R53.1, R58.2
unnamed: R159.2, R165.2, SW2.A
unnamed: IC14.8, IC14.11, R102.2
unnamed: OK3.1, R114.2
unnamed: R161.1, R162.2
unnamed: OK4.3, R116.2, R119.2
unnamed: IC34.8, R169.1, SP2.-B
unnamed: C21.+, FB1.P$1, IC2.1, R17.1, R19.1
unnamed: C159.1, D27.C, IC38.2, R183.2, R196.2
unnamed: Q14.3, R65.2
unnamed: IC14.7, IC14.9, R85.1, R90.2
unnamed: IC34.4, R173.1, R175.2
unnamed: R152.2, R153.1
unnamed: R92.2, R93.1
unnamed: OK2.2, R112.1
unnamed: OK1.2, R109.1
unnamed: C104A.2, R136A.2
unnamed: IC14.4, IC14.10, R91.1, R98.2
unnamed: C109A.2, R140A.2
unnamed: C164.2, C184.2, IC36.12, R184.2
unnamed: IC44.1, IC44.2, R187.1
unnamed: IC34.3, R169.2, R172.1
unnamed: OK6.1, R166.2
unnamed: Q10.E, R36.1
unnamed: Q9.E, R35.1
unnamed: IC29.2, JP8.3, R160.1
unnamed: Q12.E, R55.2
unnamed: F1.1, OK6.4, ZD14.C
unnamed: OK6.3, X14.1, X14.1.1, ZD14.A
unnamed: IC38.5, R191.2, R217.2, R218.1
unnamed: D21.C, IC31.7
unnamed: IC38.6, R192.2, R219.1, R222.2
unnamed: C170.1, R219.2, R221.1
unnamed: C150.1, R172.2
unnamed: C155.2, IC34.2
unnamed: C153.1, R173.2
unnamed: C168.1, R218.2, R220.1
unnamed: C153.2, R171.1
unnamed: C152.1, R170.1, R171.2
unnamed: C151.1, IC33.4, R170.2
unnamed: R65.1S, R71.1
unnamed: Q13.3, R62.1, R63.2
unnamed: C167.2, R191.1
unnamed: C169.2, R192.1
unnamed: C173.2, R194.1
unnamed: D26.C, IC39.2, R178.2, R193.2, R194.2
unnamed: C174.2, R195.1
unnamed: K_DOUT.12A, K_DOUT.12B, VAR4.2, X6.3
unnamed: OK3.2, Q24.3
unnamed: C175.2, R196.1
unnamed: D30.C, D32.A, Q34.G, R199.1
unnamed: D30.A, Q35.3
unnamed: D31.A, Q35.1, R198.1, R200.2
unnamed: D31.C, ZD16.C
unnamed: C176.1, R200.1
unnamed: D32.C, ZD17.C
unnamed: Q44.3, R203.1, R204.1, R261.1
unnamed: D33.A, Q41.C, Q44.1, R204.2
unnamed: Q40.E, R197.2
unnamed: IC44.13, IC44.14, R188.1
unnamed: IC44.5, IC44.6, R208.2
unnamed: IC44.8, IC44.11, R209.2
unnamed: IC44.7, IC44.9, R186.2, R207.1
unnamed: IC44.4, IC44.10, R185.2, R227.1
unnamed: Q39.E, R212.1
unnamed: Q38.E, R213.1
unnamed: Q36.E, R214.2
unnamed: Q40.B, R201.1, R202.2, R264.2
unnamed: Q37.3, R205.1
unnamed: Q41.B, R203.2
unnamed: C186.1, IC40.5
unnamed: IC39.6, IC39.7, JP11.1
unnamed: C159.2, R228.1
unnamed: C190.2, R231.2
unnamed: C208.2, D35.A, Q45.B, R232.1, R234.2
unnamed: D35.C, Q45.E, R233.2
unnamed: C194.1, IC41.6, R237.2
unnamed: C193.1, R237.1
unnamed: C196.1, IC41.9
unnamed: IC41.12, R271.1
unnamed: IC41.2, R235.1
unnamed: C197.2, IC41.4
unnamed: C208.1, Q45.C, Q47.3, R245.1
unnamed: C221.1, L6.1, L7.2, R238.1, R246.2
unnamed: C203.1, C231.+, FB9.P$1, IC45.12, R240.1
unnamed: IC42.6, IC43.4
unnamed: C230.2, IC43.1, R242.1
unnamed: IC41.8, R244.1
unnamed: C209.2, Q49.B, R247.1, R248.2, R265.2
unnamed: C211.2, Q49.C, R252.1, R254.2
unnamed: Q48.C, R249.1
unnamed: C210.1, Q48.B, R250.2, R251.1
unnamed: C211.1, Q50.B, R252.2, R253.2
unnamed: Q51.B, R254.1, R256.2
unnamed: C216.2, IC36.10, R257.2
unnamed: C217.2, IC36.7, R258.2
unnamed: C218.2, IC36.11, R259.2
unnamed: C219.1, IC36.6, R260.2
unnamed: R193.1, R263.2
unnamed: C157.1, R263.1
unnamed: R249.2, R265.1
unnamed: C228.2, R268.1
unnamed: C229.1, IC39.5, R269.1, R270.2
unnamed: Q46.1, R271.2
unnamed: IC45.15, R240.2, R243.1
unnamed: C199.2, IC45.16
unnamed: C200.2, IC45.3
unnamed: IC45.4, R241.2, R262.1
unnamed: C202.1, IC45.9, IC45.10
unnamed: C202.2, IC45.7, IC45.8
unnamed: LED1.A, R272.1
unnamed: Q53.3, R273.2
unnamed: IC46.7, R276.2, R277.1
unnamed: C235.+, FB10.P$1, IC46.1, R276.1, R278.1
unnamed: R225.1, R273.1S
unnamed: Q52.3, R224.1, R281.2
unnamed: IC48.1, R279.2, R280.1
unnamed: R273.2S, R281.1
unnamed: IC18.23, R130.2
NTC1: C109.2, MCU.A5, R133.1, X13.13
NTC2: C114.2, MCU.A6, R137.1, X15.13
NTC_IN: R177.1, X12.6, X12.6.1
OUT1+: C86.1, C104A.1, J1.P$1, K_SER.12B
OUT1-: C86.2, C89.2, C91.2, J4.P$1, K_PAR.14B, K_S1.7, R129.1, R136A.1, X13.17, X13.18, X13.19, X13.20, ZD7.A
OUT2+: C92.1, C93.1, C94.1, C96.1, C109A.1, J5.P$1, K_PAR.14A, K_S2.7, X15.23, X15.24, X15.25, X15.26, ZD10.C
OUT2-: C96.2, J6.P$1, K_SER.12A, R140A.1
OUT+: C36.2, C40.1, C53.1, C70.1, Q4.S, Q5.E, Q18.E, R15.2, R26.2, R28.2, R32.1, R34.2, R83.2, X2.23, X2.24, X2.25, X2.26, ZD2.A
OUT+1: C168.2, C173.1, C175.1, C209.1, Q34.S, Q41.E, Q49.E, R180.1, R199.2, R201.2, R232.2, R247.2, R261.2, X21.23, X21.24, X21.25, X21.26, ZD16.A
OUT-: C37.1, C38.2, C74.2, Q13.2, Q13.4, Q14.2, Q20.E, R59.2, R101.1, X2.17, X2.18, X2.19, X2.20
OUT-1: C170.2, C174.1, C210.2, Q48.E, Q52.2, Q52.4, Q53.2, R181.2, R250.1, X21.17, X21.18, X21.19, X21.20
POST_OE: Q16.3, R55.1
POST_OE1: Q42.3, R214.1
POUT-: C11.2, C12.2, C13.2, R65.1, SH1.P$1
POUT-1: C207.2, C221.2, C222.2, R273.1, SH4.P$1
PREG_OUT: C12.1, C13.1, L4.2, Q4.D, R8.2
PREG_OUT1: C207.1, C222.1, L6.2, Q34.D, R238.2
PRE_OE: IC8.28, Q16.1, R3.2, R75.2
PRE_OE1: IC47.28, Q42.1, R210.2, R244.2
PS_MISO: IC8.14, IC13.15, X2.9
PS_MISO1: IC36.15, IC47.14, X21.9
PS_MOSI: IC8.13, IC10.7, IC13.16, X2.1
PS_MOSI1: IC35.7, IC36.16, IC47.13, X21.1
PS_SCLK: IC8.12, IC10.6, IC13.1, X2.7
PS_SCLK1: IC35.6, IC36.1, IC47.12, X21.7
PWRDIR: IC29.12, MCU.A1
PWRGOOD: IC2.5, IC8.27, R19.2
PWRGOOD1: IC46.5, IC47.27, R278.2
PWRSS: IC29.10, MCU.A2
PWR_DIRECT: Q33.3, X16.3
PWR_EN: IC29.11, Q33.1, R158.1
PWR_IN1+: C87.1, C88.1, C89.1, K_PAR.11A, K_S1.2, X13.23, X13.24, X13.25, X13.26, ZD7.C
PWR_IN2-: C94.2, C95.2, K_PAR.11B, K_S2.2, R132.1, X15.17, X15.18, X15.19, X15.20, ZD10.A
PWR_SSTART: Q32.3, X16.4
Q7C: Q9.B, Q9.C, Q10.B, Q12.C
Q7C1: Q36.C, Q38.B, Q38.C, Q39.B
Q9C: D5.C, Q8.2, Q8.4, ZD3.A
Q9C1: D33.C, Q37.2, Q37.4, ZD17.A
RTC_SELECT: IC24.6, MCU.8
SCLK: IC18.3, IC20.5, IC23.5, IC24.10, IC25.6, IC26.33, J7.5, JP5.1, LCD1.36, MCU.ICSP_SCK, X20.3
SENSE: IC1.10, Q1.3, R4.2
SENSE1: IC41.10, Q46.3, R236.2
SENSE1+: K_S1.4, X12.5, X12.5.1
SENSE1-: K_S1.5, X12.4, X12.4.1
SENSE1_IN+: K_S1.3, X13.22
SENSE1_IN-: K_S1.6, X13.21
SENSE2+: K_S2.5, X14.5, X14.5.1
SENSE2-: K_S2.4, X14.4, X14.4.1
SENSE2_IN+: K_S2.6, X15.22
SENSE2_IN-: K_S2.3, X15.21
SENSE+: C34.1, R32.2, R44.2, R89.1, X2.22
SENSE+1: C167.1, R180.2, R220.2, R248.1, X21.22
SENSE-: C41.1, R54.2, R59.1, R96.2, X2.21
SENSE-1: C169.1, R181.1, R221.2, R251.2, X21.21
SENSE_ERR: IC8.21, Q19.C, R94.1
SENSE_ERR1: IC47.21, Q51.C, R255.1
SENSE_PROT: Q10.C, Q11.C, Q17.C, R42.2, R48.2
SENSE_PROT1: Q39.C, Q40.C, Q50.C, R198.2, R215.2
SGND: C9.1, C17.2, C18.2, IC1.3, JP1.1, R5.2, R16.2, SH2.P$1
SGND1: C193.2, C194.2, C197.1, IC41.3, JP9.1, R230.2, R235.2, SH5.P$1
SW: C14.1, D1.3, L2.1, Q1.2
SW1: C190.1, D34.3, L8.1, Q46.2
SYNC: JP1.3, X2.16
SYNC1: IC20.2, IC32.3
SYNC2: IC21.2, IC32.5, IC32.6, IC32.7
SYNC3: JP9.3, X21.16
SYNC_MASTER: IC32.1, IC32.2, MCU.4
TEMP_ANALOG: C113.2, MCU.A0, R136.1, X17.2
TEMP_FREQ1: IC28.3, R150.1
TEMP_NTC: NTC1.1, NTC1.1.1, X2.13
TEMP_NTC1: NTC2.1, NTC2.1.1, X21.13
TOCAP: C130.+, IC26.20
TOUCH_CS: IC34.1, LCD1.30, MCU.43, R174.1
TOUCH_DIN: JP6.3, MCU.42
TOUCH_DOUT: JP7.3, MCU.3
TOUCH_IRQ: LCD1.34, MCU.2
TOUCH_SCLK: JP5.3, MCU.44
U_MON: IC5.7, R51.1, R52.1, R79.1
U_MON1: IC38.7, R183.1, R222.1, R257.1
U_SERVO: D7.C, D8.A, IC5.1, R56.2, R82.1
U_SERVO1: D27.A, D28.C, IC38.1, R208.1, R228.2
U_SET: IC10.4, IC12.4
U_SET1: IC35.4, IC42.4
U_SET_OUT: IC12.5, R49.1, R77.1
U_SET_OUT1: IC42.5, R182.1, R259.1
V+: C42.2, C43.1, C44.2, C45.2, C46.2, C55.1, C56.2, C72.2, FB2.P$2, IC5.8, IC6.8, IC7.7, IC9.2, IC10.1, IC11.6, IC12.2, IC14.3, R81.1, R85.2
V+1: C156.2, C160.1, C161.2, C166.2, C172.1, C178.2, C181.2, C182.2, FB9.P$2, IC35.1, IC37.7, IC38.8, IC39.8, IC40.2, IC42.2, IC43.6, IC44.3, R184.1, R207.2
V-: C47.2, C48.2, C49.1, C50.2, C51.2, C73.2, FB3.P$2, IC5.4, IC6.4, IC7.4, IC11.3, IC14.12, R98.1
V-1: C158.2, C171.2, C177.1, C179.2, C180.2, C183.2, FB8.P$2, IC37.4, IC38.4, IC39.4, IC43.3, IC44.12, R185.1
WATCHDOG: IC31.6, MCU.5
XUSB_GND: C82.2, C83.1, C85.2, FB6.P$2, IC16.1, IC17.2, IC17.8, X9.4, X11.4
XUSB_VBUS: C83.2, FB5.P$1, IC16.4, X11.1
